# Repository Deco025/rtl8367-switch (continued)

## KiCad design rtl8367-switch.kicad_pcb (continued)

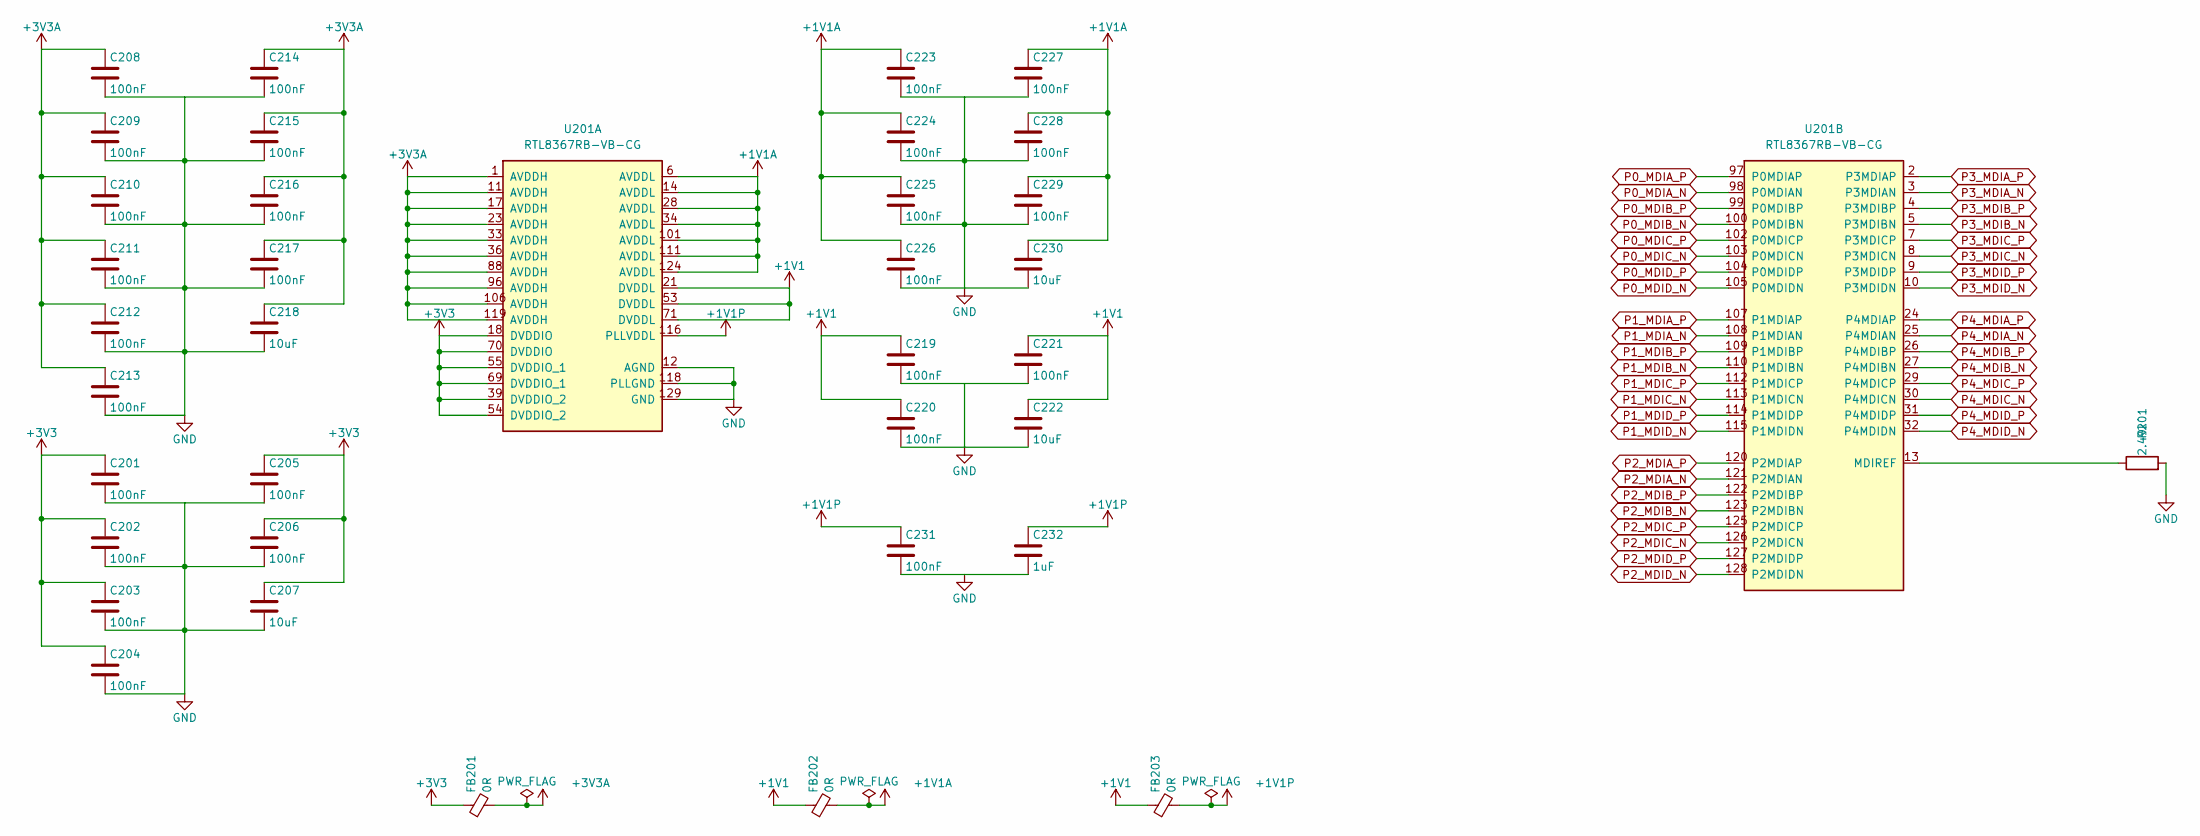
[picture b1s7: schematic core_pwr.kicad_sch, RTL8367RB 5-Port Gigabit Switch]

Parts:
C201, C202, C203, C204, C205, C206, C208, C209, C210, C211, C212, C213, C214, C215, C216, C217, C219, C220, C221, C223, C224, C225, C226, C227, C228, C229, C231: 100nF; C_0402_1005Metric; Voltage 16V
C207, C218, C222, C230: 10uF; C_0805_2012Metric; Voltage 10V
C232: 1uF; C_0603_1608Metric; Voltage 16V
FB201, FB202, FB203: 0R; R_0603_1608Metric
R201: 2.49k; R_0402_1005Metric; Tolerance 1%
U201: RTL8367RB-VB-CG; LQFP-128-1EP_14x14mm_P0.4mm_EP5.5x5.5mm_ThermalVias; MPN RTL8367RB-VB-CG; LCSC C2761412

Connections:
+1V1: C219.1, C220.1, C221.1, C222.1, FB202.1, FB203.1, U201.21 (DVDDL), U201.53 (DVDDL), U201.71 (DVDDL); also elsewhere on the board
+1V1A: C223.1, C224.1, C225.1, C226.1, C227.1, C228.1, C229.1, C230.1, FB202.2, U201.6 (AVDDL), U201.14 (AVDDL), U201.28 (AVDDL), U201.34 (AVDDL), U201.101 (AVDDL), U201.111 (AVDDL), U201.124 (AVDDL)
+1V1P: C231.1, C232.1, FB203.2, U201.116 (PLLVDDL)
+3V3: C201.1, C202.1, C203.1, C204.1, C205.1, C206.1, C207.1, FB201.1, U201.18 (DVDDIO), U201.39 (DVDDIO_2), U201.54 (DVDDIO_2), U201.55 (DVDDIO_1), U201.69 (DVDDIO_1), U201.70 (DVDDIO); also elsewhere on the board
+3V3A: C208.1, C209.1, C210.1, C211.1, C212.1, C213.1, C214.1, C215.1, C216.1, C217.1, C218.1, FB201.2, U201.1 (AVDDH), U201.11 (AVDDH), U201.17 (AVDDH), U201.23 (AVDDH), U201.33 (AVDDH), U201.36 (AVDDH), U201.88 (AVDDH), U201.96 (AVDDH), U201.106 (AVDDH), U201.119 (AVDDH); also elsewhere on the board
GND: C201.2, C202.2, C203.2, C204.2, C205.2, C206.2, C207.2, C208.2, C209.2, C210.2, C211.2, C212.2, C213.2, C214.2, C215.2, C216.2, C217.2, C218.2, C219.2, C220.2, C221.2, C222.2, C223.2, C224.2, C225.2, C226.2, C227.2, C228.2, C229.2, C230.2, C231.2, C232.2, R201.2, U201.12 (AGND), U201.118 (PLLGND), U201.129 (GND); also elsewhere on the board
unnamed: R201.1, U201.13 (MDIREF)
P0_MDIA_N: U201.98 (P0MDIAN); also elsewhere on the board
P0_MDIA_P: U201.97 (P0MDIAP); also elsewhere on the board
P0_MDIB_N: U201.100 (P0MDIBN); also elsewhere on the board
P0_MDIB_P: U201.99 (P0MDIBP); also elsewhere on the board
P0_MDIC_N: U201.103 (P0MDICN); also elsewhere on the board
P0_MDIC_P: U201.102 (P0MDICP); also elsewhere on the board
P0_MDID_N: U201.105 (P0MDIDN); also elsewhere on the board
P0_MDID_P: U201.104 (P0MDIDP); also elsewhere on the board
P1_MDIA_N: U201.108 (P1MDIAN); also elsewhere on the board
P1_MDIA_P: U201.107 (P1MDIAP); also elsewhere on the board
P1_MDIB_N: U201.110 (P1MDIBN); also elsewhere on the board
P1_MDIB_P: U201.109 (P1MDIBP); also elsewhere on the board
P1_MDIC_N: U201.113 (P1MDICN); also elsewhere on the board
P1_MDIC_P: U201.112 (P1MDICP); also elsewhere on the board
P1_MDID_N: U201.115 (P1MDIDN); also elsewhere on the board
P1_MDID_P: U201.114 (P1MDIDP); also elsewhere on the board
P2_MDIA_N: U201.121 (P2MDIAN); also elsewhere on the board
P2_MDIA_P: U201.120 (P2MDIAP); also elsewhere on the board
P2_MDIB_N: U201.123 (P2MDIBN); also elsewhere on the board
P2_MDIB_P: U201.122 (P2MDIBP); also elsewhere on the board
P2_MDIC_N: U201.126 (P2MDICN); also elsewhere on the board
P2_MDIC_P: U201.125 (P2MDICP); also elsewhere on the board
P2_MDID_N: U201.128 (P2MDIDN); also elsewhere on the board
P2_MDID_P: U201.127 (P2MDIDP); also elsewhere on the board
P3_MDIA_N: U201.3 (P3MDIAN); also elsewhere on the board
P3_MDIA_P: U201.2 (P3MDIAP); also elsewhere on the board
P3_MDIB_N: U201.5 (P3MDIBN); also elsewhere on the board
P3_MDIB_P: U201.4 (P3MDIBP); also elsewhere on the board
P3_MDIC_N: U201.8 (P3MDICN); also elsewhere on the board
P3_MDIC_P: U201.7 (P3MDICP); also elsewhere on the board
P3_MDID_N: U201.10 (P3MDIDN); also elsewhere on the board
P3_MDID_P: U201.9 (P3MDIDP); also elsewhere on the board
P4_MDIA_N: U201.25 (P4MDIAN); also elsewhere on the board
P4_MDIA_P: U201.24 (P4MDIAP); also elsewhere on the board
P4_MDIB_N: U201.27 (P4MDIBN); also elsewhere on the board
P4_MDIB_P: U201.26 (P4MDIBP); also elsewhere on the board
P4_MDIC_N: U201.30 (P4MDICN); also elsewhere on the board
P4_MDIC_P: U201.29 (P4MDICP); also elsewhere on the board
P4_MDID_N: U201.32 (P4MDIDN); also elsewhere on the board
P4_MDID_P: U201.31 (P4MDIDP); also elsewhere on the board

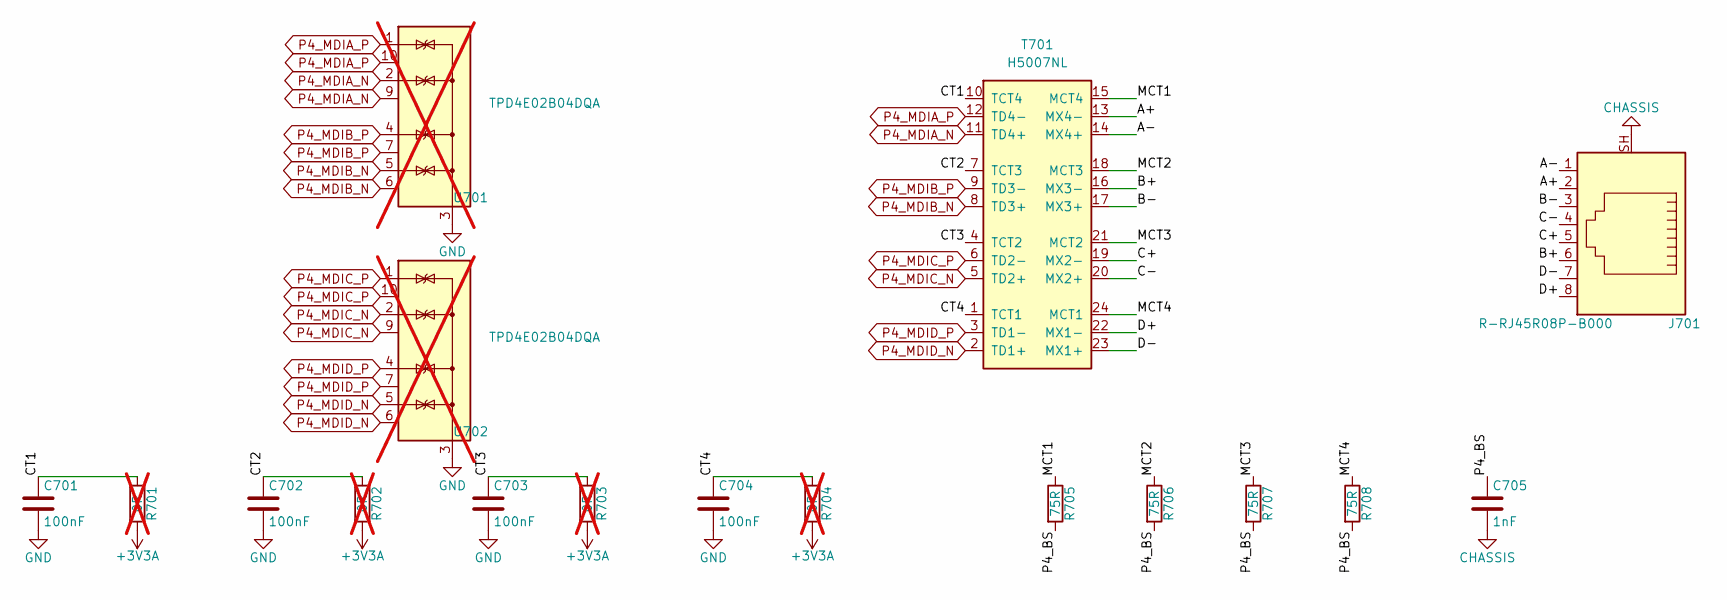
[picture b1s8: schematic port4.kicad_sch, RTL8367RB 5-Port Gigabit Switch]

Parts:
C701, C702, C703, C704: 100nF; C_0402_1005Metric; Voltage 16V
C705: 1nF; C_1206_3216Metric; Voltage 2kV
J701: R-RJ45R08P-B000; RJ45_Ckmtw_R-RJ45R08P-B000_Horizontal; MPN R-RJ45R08P-B000; LCSC C386756
R701, R702, R703, R704: 0R; R_0402_1005Metric; not fitted
R705, R706, R707, R708: 75R; R_0603_1608Metric; Tolerance 1%
T701: H5007NL; Pulse_H5007NL; MPN H5007NL; LCSC C6384935
U701, U702: TPD4E02B04DQA; USON-10_2.5x1.0mm_P0.5mm; MPN TPD4E02B04DQAR; not fitted

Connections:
+3V3A: R701.2, R702.2, R703.2, R704.2; also elsewhere on the board
/PORT4/A+: J701.2, T701.13 (MX4-)
/PORT4/A-: J701.1, T701.14 (MX4+)
/PORT4/B+: J701.6, T701.16 (MX3-)
/PORT4/B-: J701.3, T701.17 (MX3+)
/PORT4/C+: J701.5, T701.19 (MX2-)
/PORT4/C-: J701.4, T701.20 (MX2+)
/PORT4/CT1: C701.1, R701.1, T701.10 (TCT4)
/PORT4/CT2: C702.1, R702.1, T701.7 (TCT3)
/PORT4/CT3: C703.1, R703.1, T701.4 (TCT2)
/PORT4/CT4: C704.1, R704.1, T701.1 (TCT1)
/PORT4/D+: J701.8, T701.22 (MX1-)
/PORT4/D-: J701.7, T701.23 (MX1+)
/PORT4/MCT1: R705.1, T701.15 (MCT4)
/PORT4/MCT2: R706.1, T701.18 (MCT3)
/PORT4/MCT3: R707.1, T701.21 (MCT2)
/PORT4/MCT4: R708.1, T701.24 (MCT1)
/PORT4/P4_BS: C705.1, R705.2, R706.2, R707.2, R708.2
CHASSIS: C705.2, J701.SH; also elsewhere on the board
GND: C701.2, C702.2, C703.2, C704.2, U701.3 (G), U701.8 (G), U702.3 (G), U702.8 (G); also elsewhere on the board
P4_MDIA_N: T701.11 (TD4+), U701.2 (IO2), U701.9 (NC); also elsewhere on the board
P4_MDIA_P: T701.12 (TD4-), U701.1 (IO1), U701.10 (NC); also elsewhere on the board
P4_MDIB_N: T701.8 (TD3+), U701.5 (IO4), U701.6 (NC); also elsewhere on the board
P4_MDIB_P: T701.9 (TD3-), U701.4 (IO3), U701.7 (NC); also elsewhere on the board
P4_MDIC_N: T701.5 (TD2+), U702.2 (IO2), U702.9 (NC); also elsewhere on the board
P4_MDIC_P: T701.6 (TD2-), U702.1 (IO1), U702.10 (NC); also elsewhere on the board
P4_MDID_N: T701.2 (TD1+), U702.5 (IO4), U702.6 (NC); also elsewhere on the board
P4_MDID_P: T701.3 (TD1-), U702.4 (IO3), U702.7 (NC); also elsewhere on the board

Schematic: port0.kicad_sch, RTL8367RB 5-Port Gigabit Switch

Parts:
C301, C302, C303, C304: 100nF; C_0402_1005Metric; Voltage 16V
C305: 1nF; C_1206_3216Metric; Voltage 2kV
J301: R-RJ45R08P-B000; RJ45_Ckmtw_R-RJ45R08P-B000_Horizontal; MPN R-RJ45R08P-B000; LCSC C386756
R301, R302, R303, R304: 0R; R_0402_1005Metric; not fitted
R305, R306, R307, R308: 75R; R_0603_1608Metric; Tolerance 1%
T301: H5007NL; Pulse_H5007NL; MPN H5007NL; LCSC C6384935
U301, U302: TPD4E02B04DQA; USON-10_2.5x1.0mm_P0.5mm; MPN TPD4E02B04DQAR; not fitted

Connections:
+3V3A: R301.2, R302.2, R303.2, R304.2; also elsewhere on the board
/PORT0/A+: J301.2, T301.13 (MX4-)
/PORT0/A-: J301.1, T301.14 (MX4+)
/PORT0/B+: J301.6, T301.16 (MX3-)
/PORT0/B-: J301.3, T301.17 (MX3+)
/PORT0/C+: J301.5, T301.19 (MX2-)
/PORT0/C-: J301.4, T301.20 (MX2+)
/PORT0/CT1: C301.1, R301.1, T301.10 (TCT4)
/PORT0/CT2: C302.1, R302.1, T301.7 (TCT3)
/PORT0/CT3: C303.1, R303.1, T301.4 (TCT2)
/PORT0/CT4: C304.1, R304.1, T301.1 (TCT1)
/PORT0/D+: J301.8, T301.22 (MX1-)
/PORT0/D-: J301.7, T301.23 (MX1+)
/PORT0/MCT1: R305.1, T301.15 (MCT4)
/PORT0/MCT2: R306.1, T301.18 (MCT3)
/PORT0/MCT3: R307.1, T301.21 (MCT2)
/PORT0/MCT4: R308.1, T301.24 (MCT1)
/PORT0/P0_BS: C305.1, R305.2, R306.2, R307.2, R308.2
CHASSIS: C305.2, J301.SH; also elsewhere on the board
GND: C301.2, C302.2, C303.2, C304.2, U301.3 (G), U301.8 (G), U302.3 (G), U302.8 (G); also elsewhere on the board
P0_MDIA_N: T301.11 (TD4+), U301.2 (IO2), U301.9 (NC); also elsewhere on the board
P0_MDIA_P: T301.12 (TD4-), U301.1 (IO1), U301.10 (NC); also elsewhere on the board
P0_MDIB_N: T301.8 (TD3+), U301.5 (IO4), U301.6 (NC); also elsewhere on the board
P0_MDIB_P: T301.9 (TD3-), U301.4 (IO3), U301.7 (NC); also elsewhere on the board
P0_MDIC_N: T301.5 (TD2+), U302.2 (IO2), U302.9 (NC); also elsewhere on the board
P0_MDIC_P: T301.6 (TD2-), U302.1 (IO1), U302.10 (NC); also elsewhere on the board
P0_MDID_N: T301.2 (TD1+), U302.5 (IO4), U302.6 (NC); also elsewhere on the board
P0_MDID_P: T301.3 (TD1-), U302.4 (IO3), U302.7 (NC); also elsewhere on the board

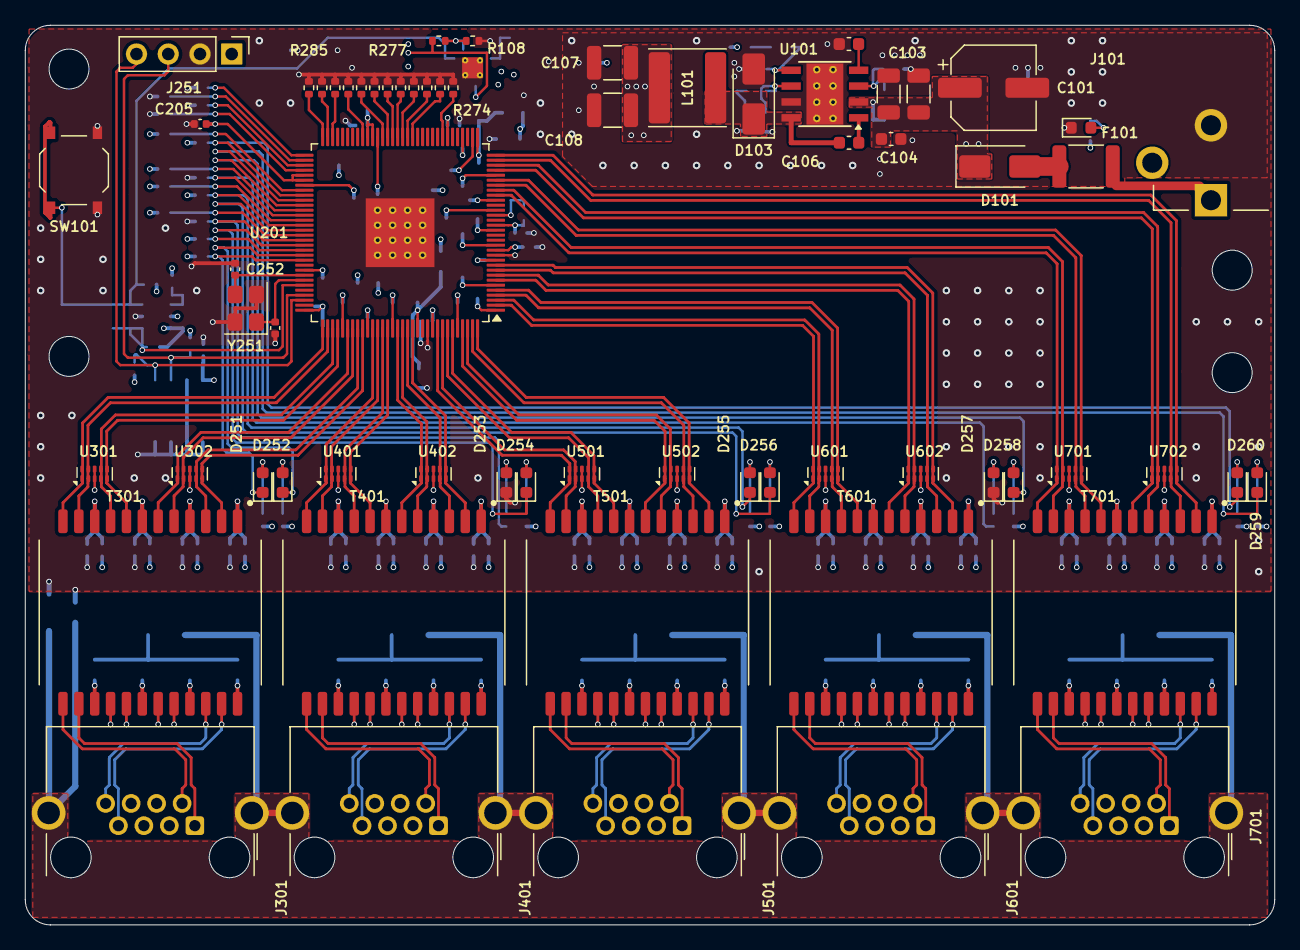
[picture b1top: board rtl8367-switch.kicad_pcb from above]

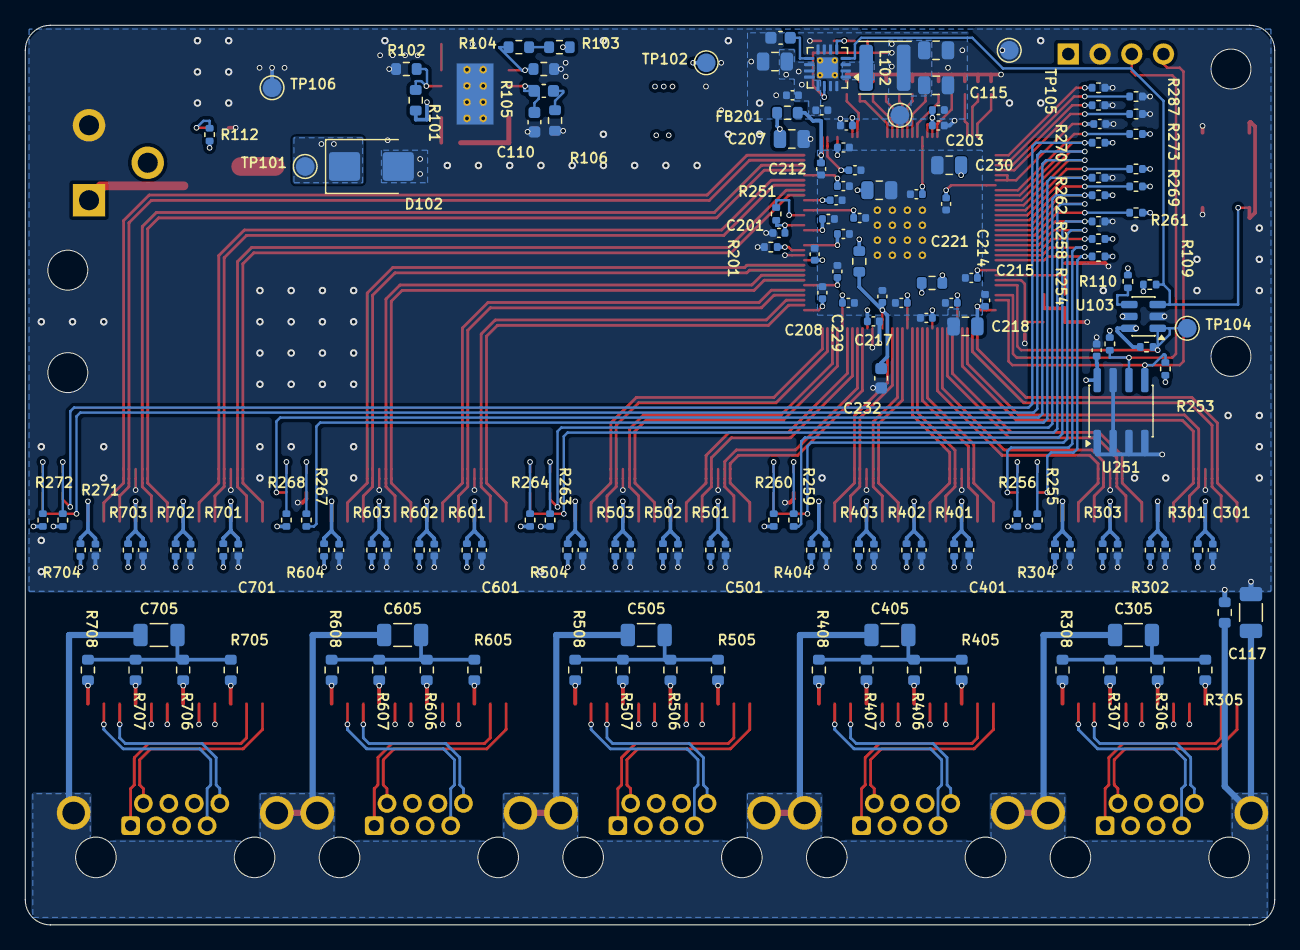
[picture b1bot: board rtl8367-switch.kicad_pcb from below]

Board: 4 copper layers, 100.0 x 72.0 mm, 229 parts (159 on the bottom side), 197 nets.

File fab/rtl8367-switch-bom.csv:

"Refs","Value","Voltage","Footprint","Qty"
"C101","47uF","25V","Capacitor_SMD:CP_Elec_6.3x7.7","1"
"C102,C103","4.7uF","25V","Capacitor_SMD:C_1206_3216Metric","2"
"C104","10nF","50V","Capacitor_SMD:C_0603_1608Metric","1"
"C105,C113","22nF","16V","Capacitor_SMD:C_0603_1608Metric","2"
"C106","100nF","50V","Capacitor_SMD:C_0603_1608Metric","1"
"C107,C108","47uF","10V","Capacitor_SMD:C_1210_3225Metric","2"
"C109","1nF","50V","Capacitor_SMD:C_0603_1608Metric","1"
"C110","47pF","50V","Capacitor_SMD:C_0603_1608Metric","1"
"C111,C207,C218,C222,C230","10uF","10V","Capacitor_SMD:C_0805_2012Metric","5"
"C112,C116,C201-C206,C208-C217,C219-C221,C223-C229,C231,C301-C304,C401-C404,C501-C504,C601-C604,C701-C704","100nF","16V","Capacitor_SMD:C_0402_1005Metric","49"
"C114,C115","22uF","6.3V","Capacitor_SMD:C_0805_2012Metric","2"
"C232","1uF","16V","Capacitor_SMD:C_0603_1608Metric","1"
"C251,C252","18pF","50V","Capacitor_SMD:C_0402_1005Metric","2"
"C305,C405,C505,C605,C705","1nF","2kV","Capacitor_SMD:C_1206_3216Metric","5"
"D101,D103","SS34","","Diode_SMD:D_SMA","2"
"D102","SMBJ15A","","Diode_SMD:D_SMB","1"
"D104,D251,D253,D255,D257,D259","Green","","LED_SMD:LED_0603_1608Metric","6"
"D252,D254,D256,D258,D260","Yellow","","LED_SMD:LED_0603_1608Metric","5"
"F101","1812L075/33DR","","Fuse:Fuse_1812_4532Metric","1"
"FB201-FB203,R103","0R","","Resistor_SMD:R_0603_1608Metric","4"
"J101","PJ-102AH","","Connector_BarrelJack:BarrelJack_CUI_PJ-102AH_Horizontal","1"
"J251","J_DBG","","Connector_PinHeader_2.54mm:PinHeader_1x04_P2.54mm_Vertical","1"
"J301,J401,J501,J601,J701","R-RJ45R08P-B000","","rtl8367-switch:RJ45_Ckmtw_R-RJ45R08P-B000_Horizontal","5"
"L101","6.8uH","","Inductor_SMD:L_Sunlord_SWPA6045S","1"
"L102","2.2uH","","Inductor_SMD:L_Sunlord_SWPA4030S","1"
"R101","332k","","Resistor_SMD:R_0603_1608Metric","1"
"R102","68.1k","","Resistor_SMD:R_0603_1608Metric","1"
"R104","10.2k","","Resistor_SMD:R_0603_1608Metric","1"
"R105","3.24k","","Resistor_SMD:R_0603_1608Metric","1"
"R106","29.4k","","Resistor_SMD:R_0603_1608Metric","1"
"R107","30.1k","","Resistor_SMD:R_0402_1005Metric","1"
"R108","80.6k","","Resistor_SMD:R_0402_1005Metric","1"
"R109,R111","10k","","Resistor_SMD:R_0402_1005Metric","2"
"R110","100k","","Resistor_SMD:R_0402_1005Metric","1"
"R112","1.5k","","Resistor_SMD:R_0402_1005Metric","1"
"R201","2.49k","","Resistor_SMD:R_0402_1005Metric","1"
"R251-R254,R257,R258,R261,R262,R265,R266,R269,R270,R273","4.7k","","Resistor_SMD:R_0402_1005Metric","13"
"R255,R256,R259,R260,R263,R264,R267,R268,R271,R272","470R","","Resistor_SMD:R_0402_1005Metric","10"
"R274-R289","1k","","Resistor_SMD:R_0402_1005Metric","16"
"R305-R308,R405-R408,R505-R508,R605-R608,R705-R708","75R","","Resistor_SMD:R_0603_1608Metric","20"
"SW101","RESET","","Button_Switch_SMD:SW_Push_1P1T_XKB_TS-1187A","1"
"T301,T401,T501,T601,T701","H5007NL","","rtl8367-switch:Pulse_H5007NL","5"
"U101","TPS54331DDA","","Package_SO:Texas_HSOP-8-1EP_3.9x4.9mm_P1.27mm_ThermalVias","1"
"U102","TPS62130A","","Package_DFN_QFN:VQFN-16-1EP_3x3mm_P0.5mm_EP1.68x1.68mm_ThermalVias","1"
"U103","TPS3808G30DBVR","","Package_TO_SOT_SMD:SOT-23-6","1"
"U201","RTL8367RB-VB-CG","","rtl8367-switch:LQFP-128-1EP_14x14mm_P0.4mm_EP5.5x5.5mm_ThermalVias","1"
"Y251","25MHz","","Crystal:Crystal_SMD_3225-4Pin_3.2x2.5mm","1"
